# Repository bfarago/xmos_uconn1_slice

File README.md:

# xmos_uconn1_slice
Adapter board for xmos jtag and xlink slice to xsys and CMOD and PMOD.

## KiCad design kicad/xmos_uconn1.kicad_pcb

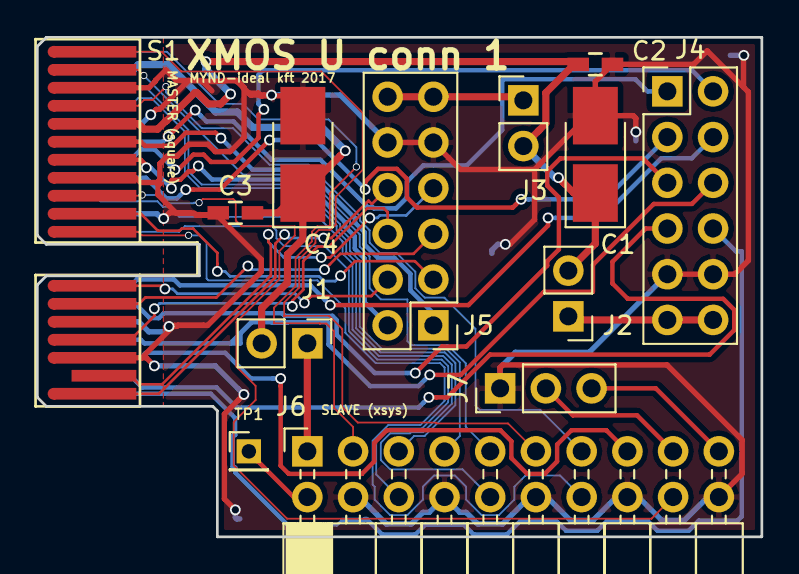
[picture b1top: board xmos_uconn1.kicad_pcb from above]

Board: 4 copper layers, 40.2 x 27.8 mm, 13 parts (0 on the bottom side), 35 nets.

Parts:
C1, C4: 2u2; CP_Tantalum_Case-B_EIA-3528-21_Hand
C2, C3: 100N; C_0603_HandSoldering
J1: CONN_PWR_B; Pin_Header_Straight_1x02_Pitch2.54mm
J2: CONN_PWR_C; Pin_Header_Straight_1x02_Pitch2.54mm
J3: CONN_PWR_D; Pin_Header_Straight_1x02_Pitch2.54mm
J4, J5: CONN_02X06; Pin_Header_Straight_2x06_Pitch2.54mm
J6: CONN_02X10; Socket_Strip_Angled_2x10_Pitch2.54mm
J7: CONN_UART; Pin_Header_Straight_1x03_Pitch2.54mm
S1: SlicePcbCon; PCI-EXPRESS
TP1: nc; Pin_Header_Straight_1x01_Pitch2.00mm

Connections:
+3V3: C1.1, C2.1, J2.2, J3.2, S1.B5
+5V: C3.1, C4.1, J1.2, S1.A2
/CD1: J4.1, S1.A6
/CD2: J4.2, S1.A7
/CD3: J4.3, S1.A8
/CD4: J4.4, S1.A12
/CD5: J4.5, S1.A13
/CD6: J4.6, S1.A15
/CD7: J4.7, S1.A17
/CD8: J4.8, S1.A18
/DD1: J5.1, S1.B6
/DD2: J5.2, S1.B7
/DD3: J5.3, S1.B10
/DD4: J5.4, S1.B12
/DD5: J5.5, S1.B13
/DD6: J5.6, S1.B15
/DD7: J5.7, S1.B17
/DD8: J5.8, S1.B18
/DEBUG_N: J6.11, S1.B1
/MSEL: J6.3, S1.A1
/TCK: J6.9, S1.B2
/TDI: J6.13, S1.B4
/TDO: J6.5, S1.A4
/TMS: J6.7, S1.A3
/XSYS_UART_RX: J6.17, J7.2
/XSYS_UART_TX: J6.19, J7.3
/XSYS_XL_DN0: J6.14, S1.B11
/XSYS_XL_DN1: J6.18, S1.B9
/XSYS_XL_UP0: J6.10, S1.A9
/XSYS_XL_UP1: J6.6, S1.A11
GND: C1.2, C2.2, C3.2, C4.2, J4.9, J4.10, J5.9, J5.10, J6.4, J6.8, J6.12, J6.16, J6.20, J7.1, S1.A5, S1.A10, S1.A14, S1.B3, S1.B8, S1.B16
unnamed: J1.1, J6.1
unnamed: J2.1, J4.11, J4.12
unnamed: J3.1, J5.11, J5.12
unnamed: J6.2, TP1.1

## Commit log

2017-06-03 This was the initial version of the files.
2017-06-04 Fix SliceCon A17,A17 swap. Remove duplicated lib entry, add slice.lib to project.
2017-06-07 xn file update
